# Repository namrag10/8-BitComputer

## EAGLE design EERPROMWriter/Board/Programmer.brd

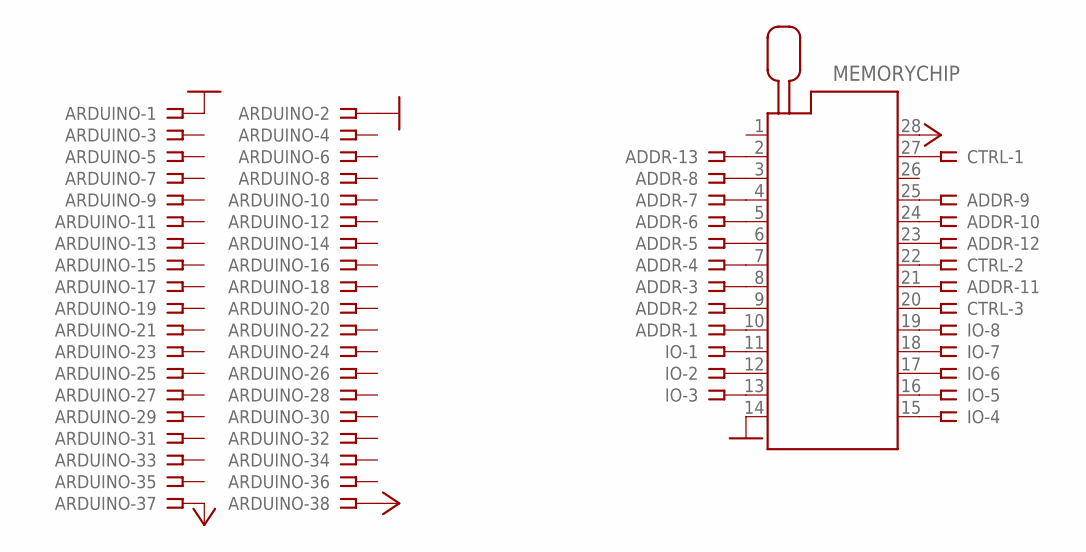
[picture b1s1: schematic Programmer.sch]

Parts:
ADDR: SSW-113-02-G-S-RA
ARDUINO: SSW-119-02-G-D
CTRL: SSW-103-02-G-S-RA
IO: SSW-108-02-G-S-RA
MEMORYCHIP: 228-1277-00-0602J

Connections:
GND: ARDUINO.1, ARDUINO.2, MEMORYCHIP.14
unnamed: IO.1, MEMORYCHIP.11
unnamed: IO.2, MEMORYCHIP.12
unnamed: IO.3, MEMORYCHIP.13
unnamed: IO.4, MEMORYCHIP.15
unnamed: IO.5, MEMORYCHIP.16
unnamed: IO.6, MEMORYCHIP.17
unnamed: IO.7, MEMORYCHIP.18
unnamed: IO.8, MEMORYCHIP.19
unnamed: ADDR.1, MEMORYCHIP.10
unnamed: ADDR.2, MEMORYCHIP.9
unnamed: ADDR.3, MEMORYCHIP.8
unnamed: ADDR.4, MEMORYCHIP.7
unnamed: ADDR.5, MEMORYCHIP.6
unnamed: ADDR.6, MEMORYCHIP.5
unnamed: ADDR.7, MEMORYCHIP.4
unnamed: ADDR.8, MEMORYCHIP.3
unnamed: ADDR.9, MEMORYCHIP.25
unnamed: ADDR.10, MEMORYCHIP.24
unnamed: ADDR.11, MEMORYCHIP.21
unnamed: ADDR.12, MEMORYCHIP.23
unnamed: ADDR.13, MEMORYCHIP.2
unnamed: CTRL.1, MEMORYCHIP.27
unnamed: CTRL.2, MEMORYCHIP.22
unnamed: CTRL.3, MEMORYCHIP.20
VCC: ARDUINO.37, ARDUINO.38, MEMORYCHIP.28

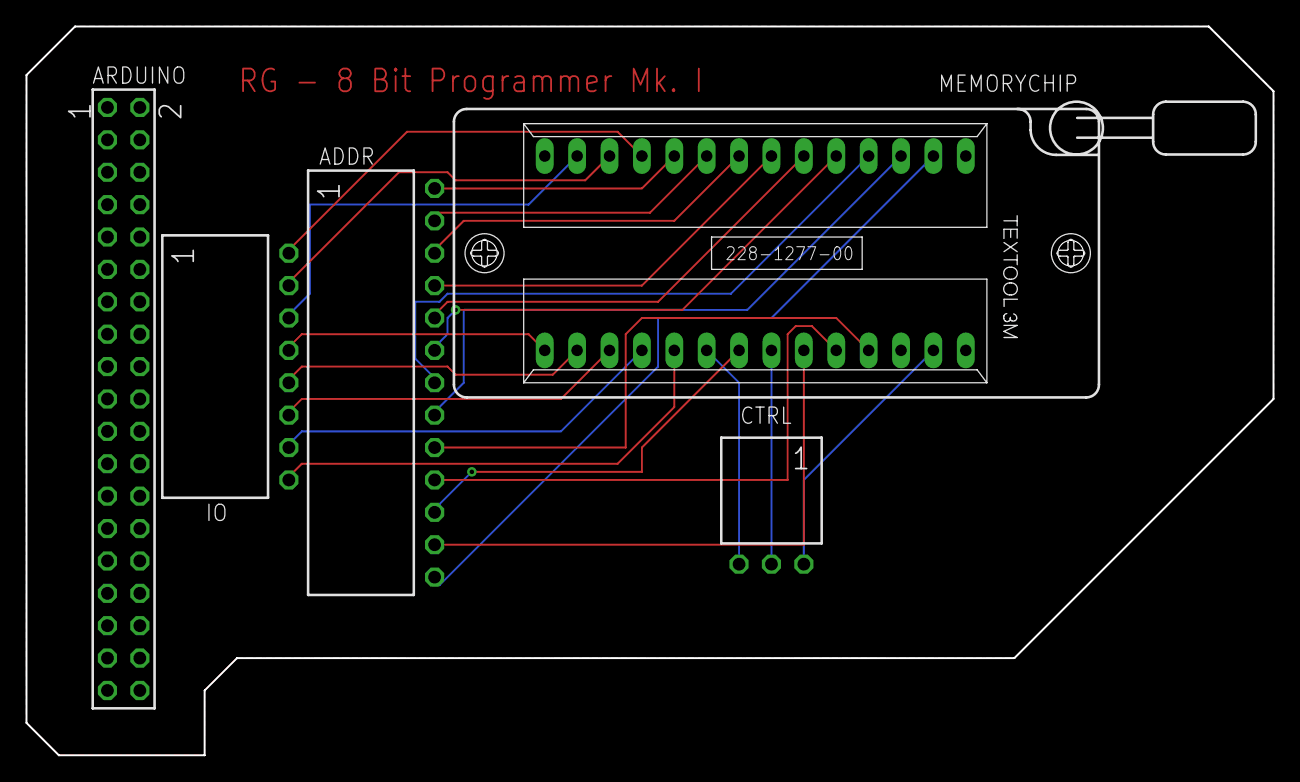
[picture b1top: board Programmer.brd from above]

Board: 2 copper layers, 97.8 x 57.1 mm, 5 parts (0 on the bottom side), 26 nets.

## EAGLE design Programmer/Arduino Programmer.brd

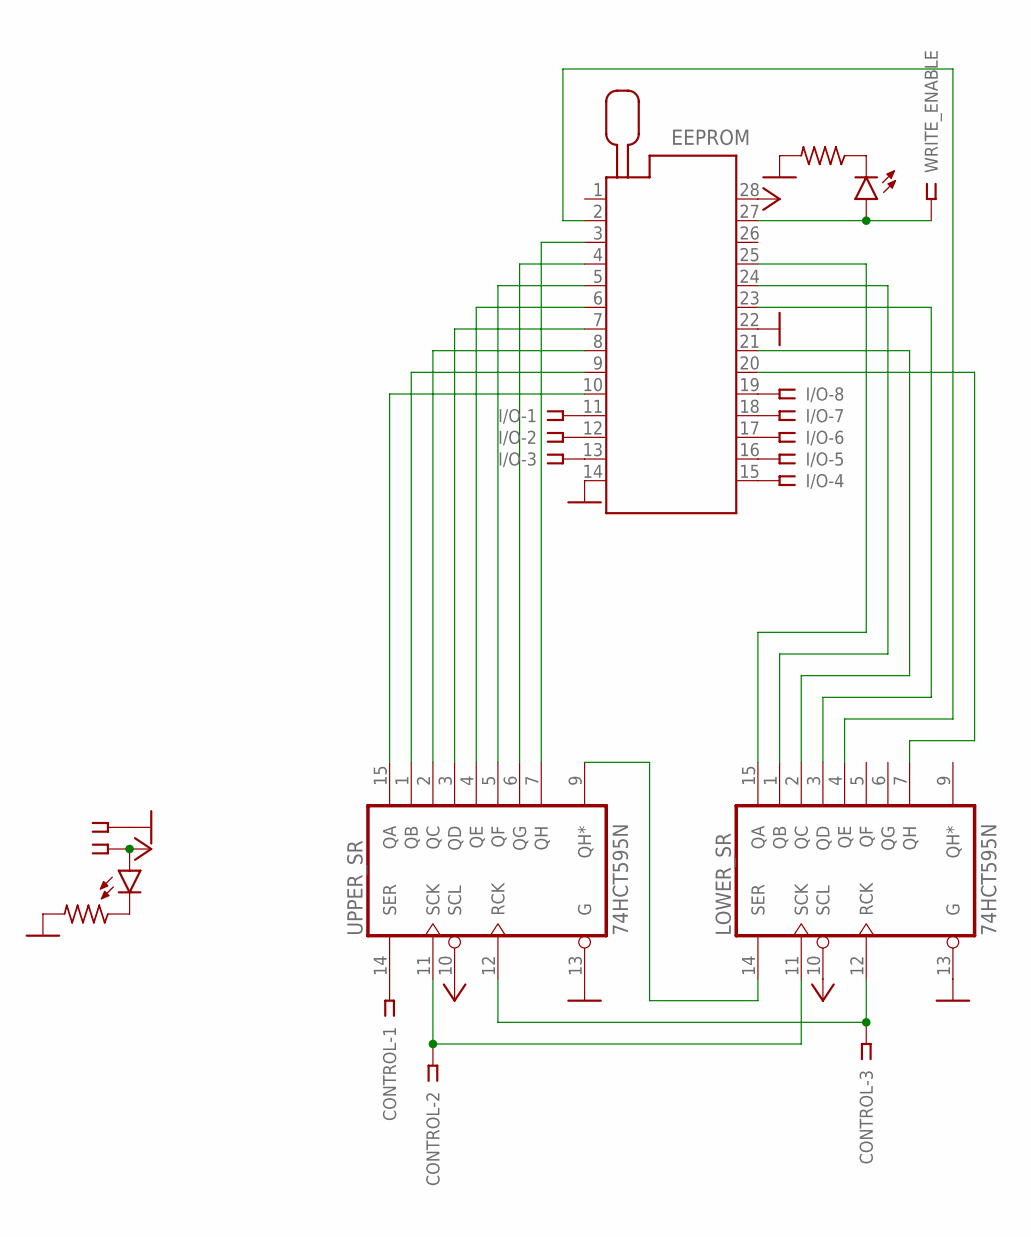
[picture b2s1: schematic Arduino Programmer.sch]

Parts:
CLK: LED5MM
CONTROL: SSW-101-02-G-T
EEPROM: 228-1277-00-0602J
I/O: SSW-108-02-G-S
LOWER_SR: 74HCT595N; DIL16
POWER: LED5MM
R1, R2: R-US_0204/7; 0204/7
UPPER_SR: 74HCT595N; DIL16
WRITE_ENABLE: SSW-101-02-G-S
X2: SSW-102-02-G-S

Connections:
GND: EEPROM.14, EEPROM.22, LOWER_SR.8 (GND), LOWER_SR.13 (G), R1.2, R2.2, UPPER_SR.8 (GND), UPPER_SR.13 (G), X2.1
unnamed: CONTROL.3, LOWER_SR.12 (RCK), UPPER_SR.12 (RCK)
unnamed: CONTROL.2, LOWER_SR.11 (SCK), UPPER_SR.11 (SCK)
unnamed: LOWER_SR.14 (SER), UPPER_SR.9 (QH*)
unnamed: CONTROL.1, UPPER_SR.14 (SER)
unnamed: EEPROM.10, UPPER_SR.15 (QA)
unnamed: EEPROM.9, UPPER_SR.1 (QB)
unnamed: EEPROM.8, UPPER_SR.2 (QC)
unnamed: EEPROM.7, UPPER_SR.3 (QD)
unnamed: EEPROM.6, UPPER_SR.4 (QE)
unnamed: EEPROM.5, UPPER_SR.5 (QF)
unnamed: EEPROM.4, UPPER_SR.6 (QG)
unnamed: EEPROM.3, UPPER_SR.7 (QH)
unnamed: EEPROM.25, LOWER_SR.15 (QA)
unnamed: EEPROM.24, LOWER_SR.1 (QB)
unnamed: EEPROM.21, LOWER_SR.2 (QC)
unnamed: EEPROM.23, LOWER_SR.3 (QD)
unnamed: EEPROM.2, LOWER_SR.4 (QE)
unnamed: EEPROM.20, LOWER_SR.7 (QH)
unnamed: EEPROM.16, I/O.5
unnamed: EEPROM.17, I/O.6
unnamed: EEPROM.18, I/O.7
unnamed: EEPROM.19, I/O.8
unnamed: EEPROM.11, I/O.1
unnamed: EEPROM.12, I/O.2
unnamed: EEPROM.13, I/O.3
unnamed: EEPROM.15, I/O.4
unnamed: CLK.A, EEPROM.27, WRITE_ENABLE.1
unnamed: CLK.K (C), R1.1
unnamed: POWER.K (C), R2.1
VCC: EEPROM.28, LOWER_SR.10 (SCL), LOWER_SR.16 (VCC), POWER.A, UPPER_SR.10 (SCL), UPPER_SR.16 (VCC), X2.2

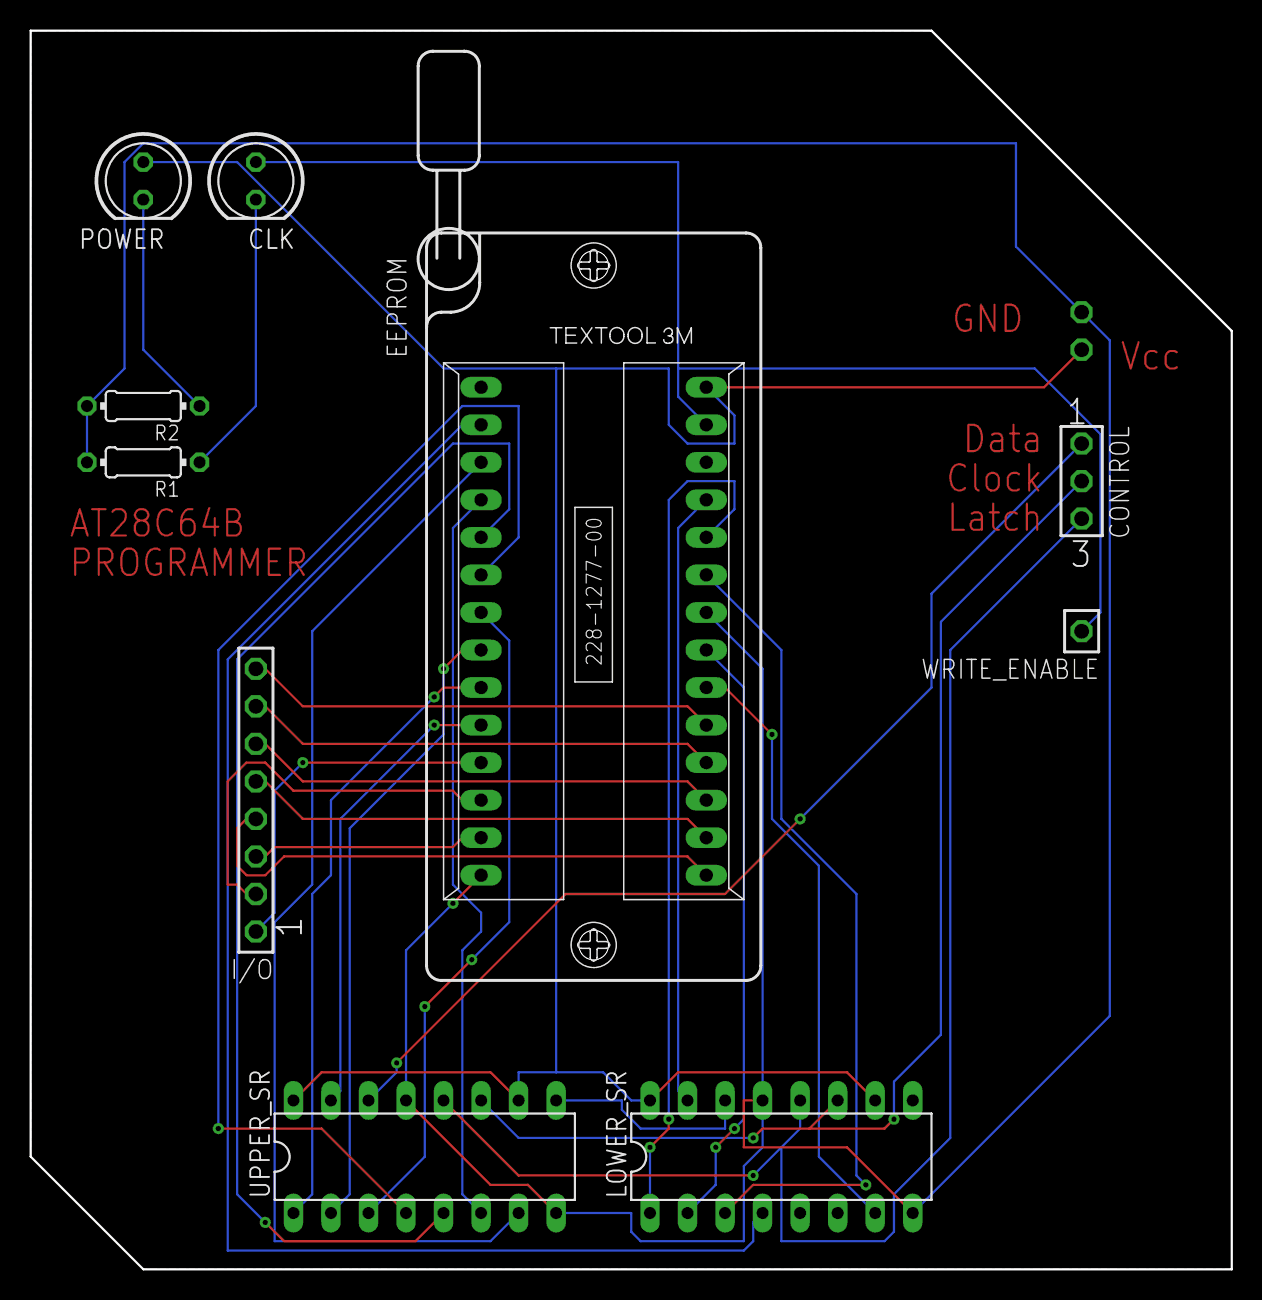
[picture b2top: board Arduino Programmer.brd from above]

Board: 2 copper layers, 81.3 x 83.8 mm, 11 parts (1 on the bottom side), 31 nets.

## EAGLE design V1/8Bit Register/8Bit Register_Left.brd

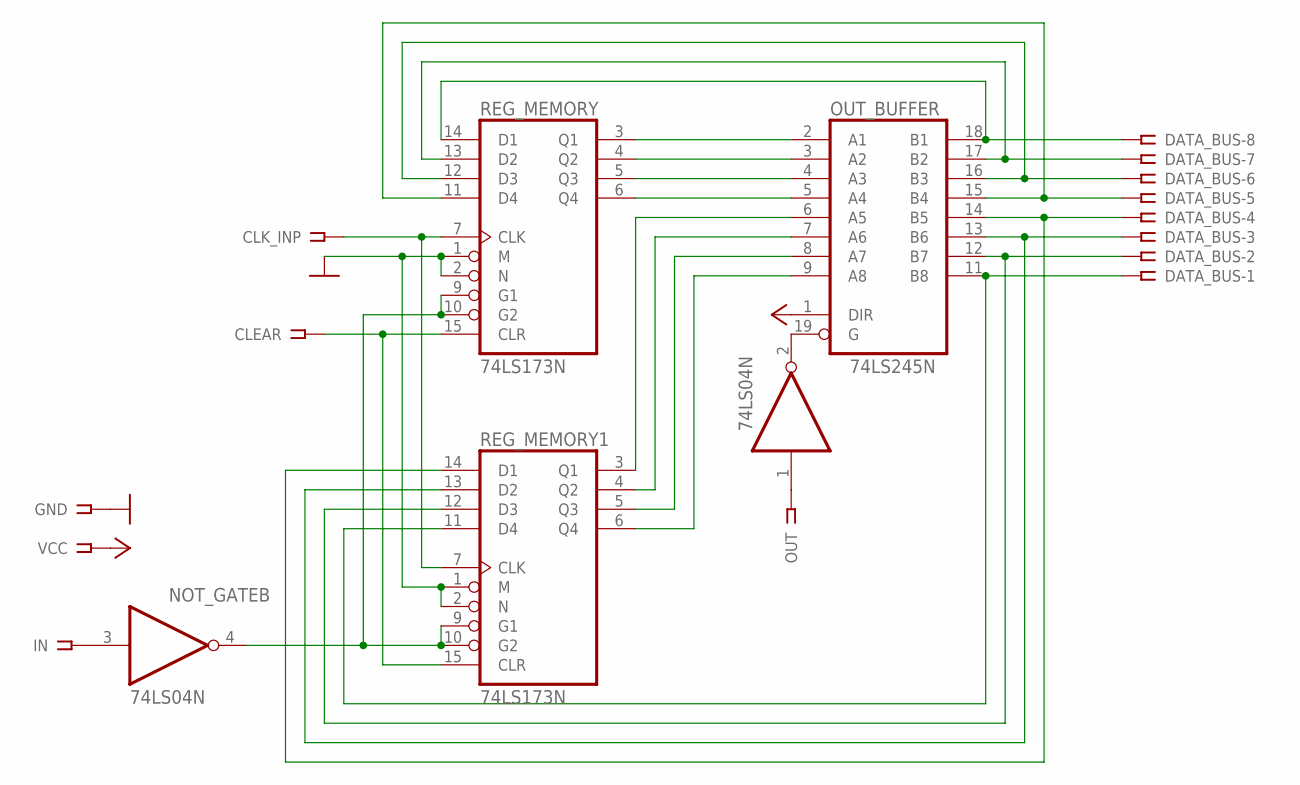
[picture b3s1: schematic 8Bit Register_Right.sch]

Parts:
CLEAR: SSW-101-02-G-S-RA
CLK_INP: SSW-101-02-G-S-RA
DATA_BUS: SSW-108-02-G-S
GND: SSW-101-02-G-S-RA
IN: SSW-101-02-G-S-RA
NOT_GATE: 74LS04N; DIL14
OUT: SSW-101-02-G-S-RA
OUT_BUFFER: 74LS245N; DIL20
REG_MEMORY, REG_MEMORY1: 74LS173N; DIL16
VCC: SSW-101-02-G-S-RA

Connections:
GND: GND.1, NOT_GATE.7 (GND), OUT_BUFFER.10 (GND), REG_MEMORY.1 (M), REG_MEMORY.2 (N), REG_MEMORY.8 (GND), REG_MEMORY1.1 (M), REG_MEMORY1.2 (N), REG_MEMORY1.8 (GND)
unnamed: CLK_INP.1, REG_MEMORY.7 (CLK), REG_MEMORY1.7 (CLK)
unnamed: NOT_GATE.1 (I), OUT.1
unnamed: CLEAR.1, REG_MEMORY.15 (CLR), REG_MEMORY1.15 (CLR)
unnamed: OUT_BUFFER.2 (A1), REG_MEMORY.3 (Q1)
unnamed: OUT_BUFFER.3 (A2), REG_MEMORY.4 (Q2)
unnamed: OUT_BUFFER.4 (A3), REG_MEMORY.5 (Q3)
unnamed: OUT_BUFFER.5 (A4), REG_MEMORY.6 (Q4)
unnamed: OUT_BUFFER.6 (A5), REG_MEMORY1.3 (Q1)
unnamed: OUT_BUFFER.7 (A6), REG_MEMORY1.4 (Q2)
unnamed: OUT_BUFFER.8 (A7), REG_MEMORY1.5 (Q3)
unnamed: OUT_BUFFER.9 (A8), REG_MEMORY1.6 (Q4)
unnamed: NOT_GATE.2 (O), OUT_BUFFER.19 (G)
unnamed: DATA_BUS.8, OUT_BUFFER.18 (B1), REG_MEMORY.14 (D1)
unnamed: DATA_BUS.7, OUT_BUFFER.17 (B2), REG_MEMORY.13 (D2)
unnamed: NOT_GATE.4 (O), REG_MEMORY.9 (G1), REG_MEMORY.10 (G2), REG_MEMORY1.9 (G1), REG_MEMORY1.10 (G2)
unnamed: DATA_BUS.6, OUT_BUFFER.16 (B3), REG_MEMORY.12 (D3)
unnamed: DATA_BUS.5, OUT_BUFFER.15 (B4), REG_MEMORY.11 (D4)
unnamed: DATA_BUS.1, OUT_BUFFER.11 (B8), REG_MEMORY1.11 (D4)
unnamed: DATA_BUS.2, OUT_BUFFER.12 (B7), REG_MEMORY1.12 (D3)
unnamed: DATA_BUS.3, OUT_BUFFER.13 (B6), REG_MEMORY1.13 (D2)
unnamed: DATA_BUS.4, OUT_BUFFER.14 (B5), REG_MEMORY1.14 (D1)
unnamed: IN.1, NOT_GATE.3 (I)
VCC: NOT_GATE.14 (VCC), OUT_BUFFER.1 (DIR), OUT_BUFFER.20 (VCC), REG_MEMORY.16 (VCC), REG_MEMORY1.16 (VCC), VCC.1

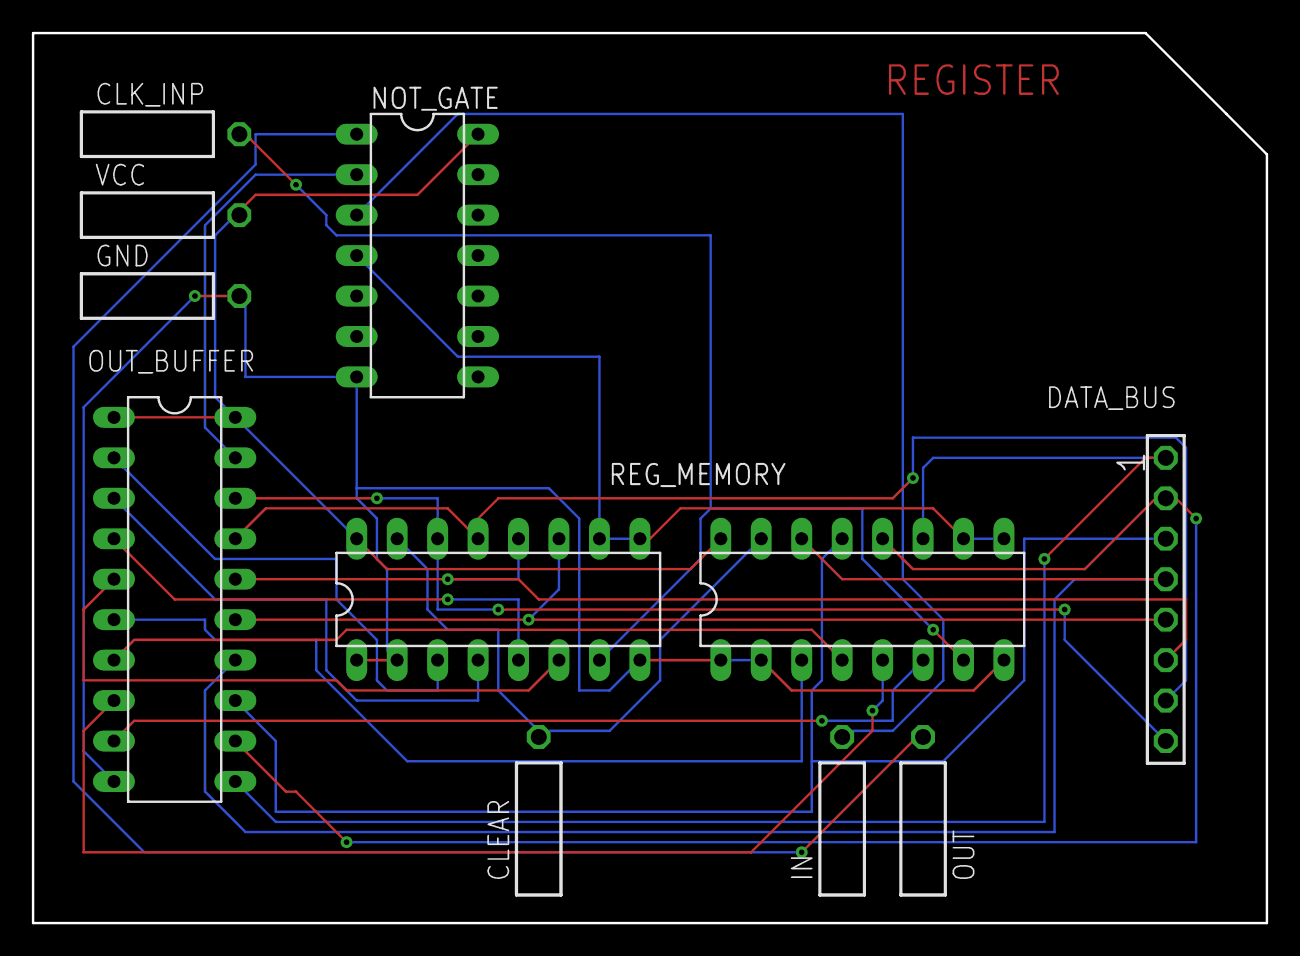
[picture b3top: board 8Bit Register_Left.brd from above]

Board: 2 copper layers, 77.5 x 55.9 mm, 11 parts (0 on the bottom side), 24 nets.

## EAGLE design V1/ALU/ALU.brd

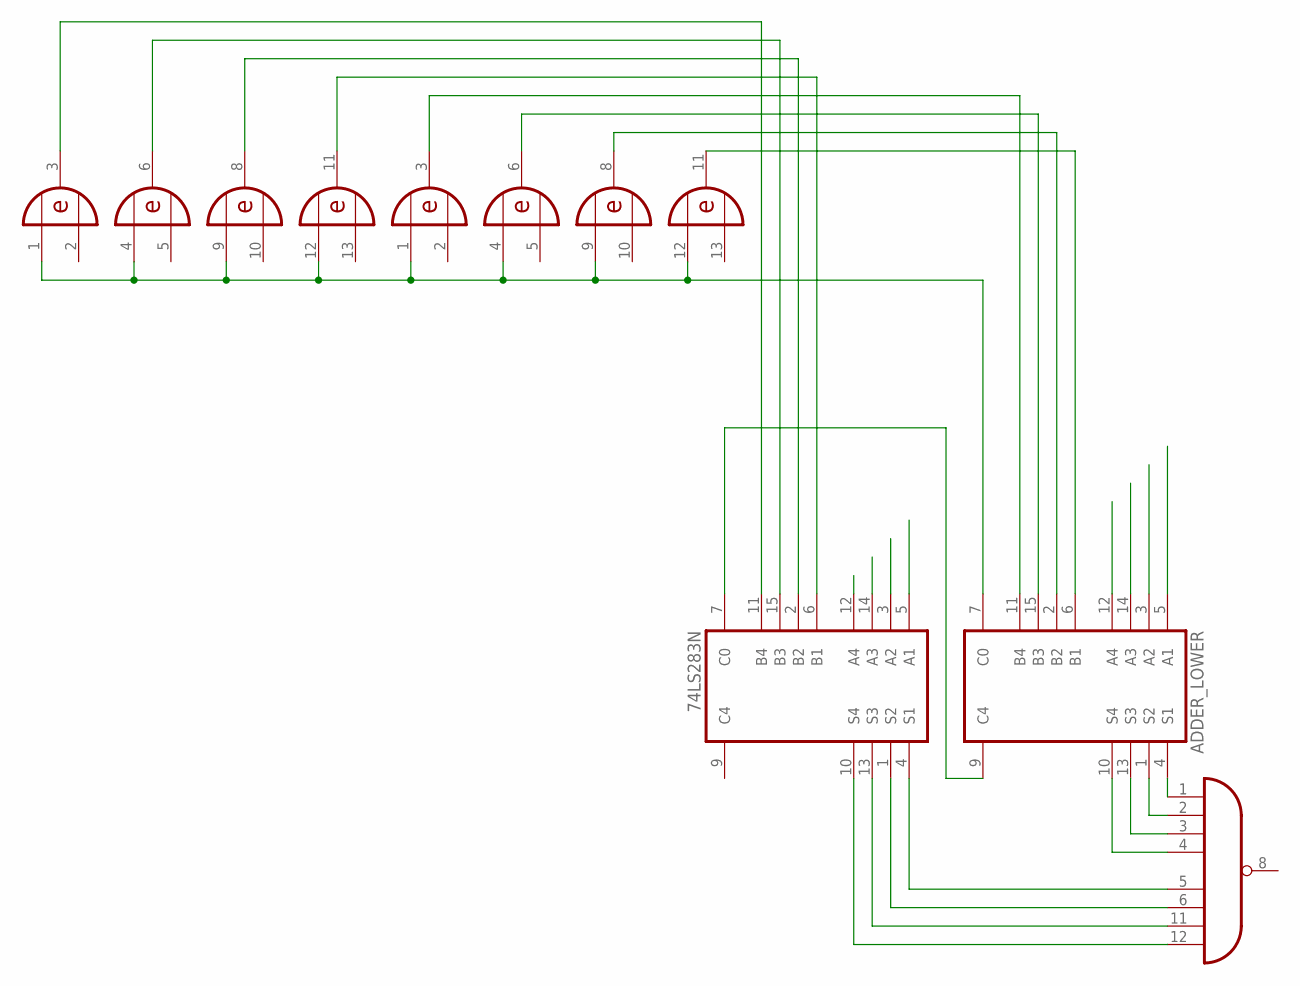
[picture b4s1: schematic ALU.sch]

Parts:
ADDER_LOWER: 74LS283N; DIL16
ADDER_UPPER: 74LS283N; DIL16
AND_GATE1: 74LS30N; DIL14
SUBTRACT_INVERTER_LOWER: 74LS86N; DIL14
SUBTRACT_INVERTER_UPPER: 74LS86N; DIL14

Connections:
GND: ADDER_LOWER.8 (GND), ADDER_UPPER.8 (GND), AND_GATE1.7 (GND), SUBTRACT_INVERTER_LOWER.7 (GND), SUBTRACT_INVERTER_UPPER.7 (GND)
unnamed: ADDER_LOWER.10 (S4), AND_GATE1.4 (I3)
unnamed: ADDER_LOWER.13 (S3), AND_GATE1.3 (I2)
unnamed: ADDER_LOWER.1 (S2), AND_GATE1.2 (I1)
unnamed: ADDER_LOWER.4 (S1), AND_GATE1.1 (I0)
unnamed: ADDER_LOWER.6 (B1), SUBTRACT_INVERTER_LOWER.11 (O)
unnamed: ADDER_LOWER.2 (B2), SUBTRACT_INVERTER_LOWER.8 (O)
unnamed: ADDER_LOWER.15 (B3), SUBTRACT_INVERTER_LOWER.6 (O)
unnamed: ADDER_LOWER.11 (B4), SUBTRACT_INVERTER_LOWER.3 (O)
unnamed: ADDER_UPPER.6 (B1), SUBTRACT_INVERTER_UPPER.11 (O)
unnamed: ADDER_UPPER.2 (B2), SUBTRACT_INVERTER_UPPER.8 (O)
unnamed: ADDER_UPPER.15 (B3), SUBTRACT_INVERTER_UPPER.6 (O)
unnamed: ADDER_UPPER.11 (B4), SUBTRACT_INVERTER_UPPER.3 (O)
REG_A_1PLACE: ADDER_LOWER.5 (A1)
REG_A_2PLACE: ADDER_LOWER.3 (A2)
REG_A_4PLACE: ADDER_LOWER.14 (A3)
REG_A_8PLACE: ADDER_LOWER.12 (A4)
REG_A_16PLACE: ADDER_UPPER.5 (A1)
REG_A_32PLACE: ADDER_UPPER.3 (A2)
REG_A_64PLACE: ADDER_UPPER.14 (A3)
REG_A_128PLACE: ADDER_UPPER.12 (A4)
SUBTRACT: ADDER_LOWER.7 (C0), SUBTRACT_INVERTER_LOWER.1 (I0), SUBTRACT_INVERTER_LOWER.4 (I0), SUBTRACT_INVERTER_LOWER.9 (I0), SUBTRACT_INVERTER_LOWER.12 (I0), SUBTRACT_INVERTER_UPPER.1 (I0), SUBTRACT_INVERTER_UPPER.4 (I0), SUBTRACT_INVERTER_UPPER.9 (I0), SUBTRACT_INVERTER_UPPER.12 (I0)
SUM_16: ADDER_UPPER.4 (S1), AND_GATE1.5 (I4)
SUM_32: ADDER_UPPER.1 (S2), AND_GATE1.6 (I5)
SUM_64: ADDER_UPPER.13 (S3), AND_GATE1.11 (I6)
SUM_128: ADDER_UPPER.10 (S4), AND_GATE1.12 (I7)
SUM_CARRY: ADDER_LOWER.9 (C4), ADDER_UPPER.7 (C0)
VCC: ADDER_LOWER.16 (VCC), ADDER_UPPER.16 (VCC), AND_GATE1.14 (VCC), SUBTRACT_INVERTER_LOWER.14 (VCC), SUBTRACT_INVERTER_UPPER.14 (VCC)

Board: 2 copper layers, 5 parts (0 on the bottom side), 20 nets, no tracks yet.

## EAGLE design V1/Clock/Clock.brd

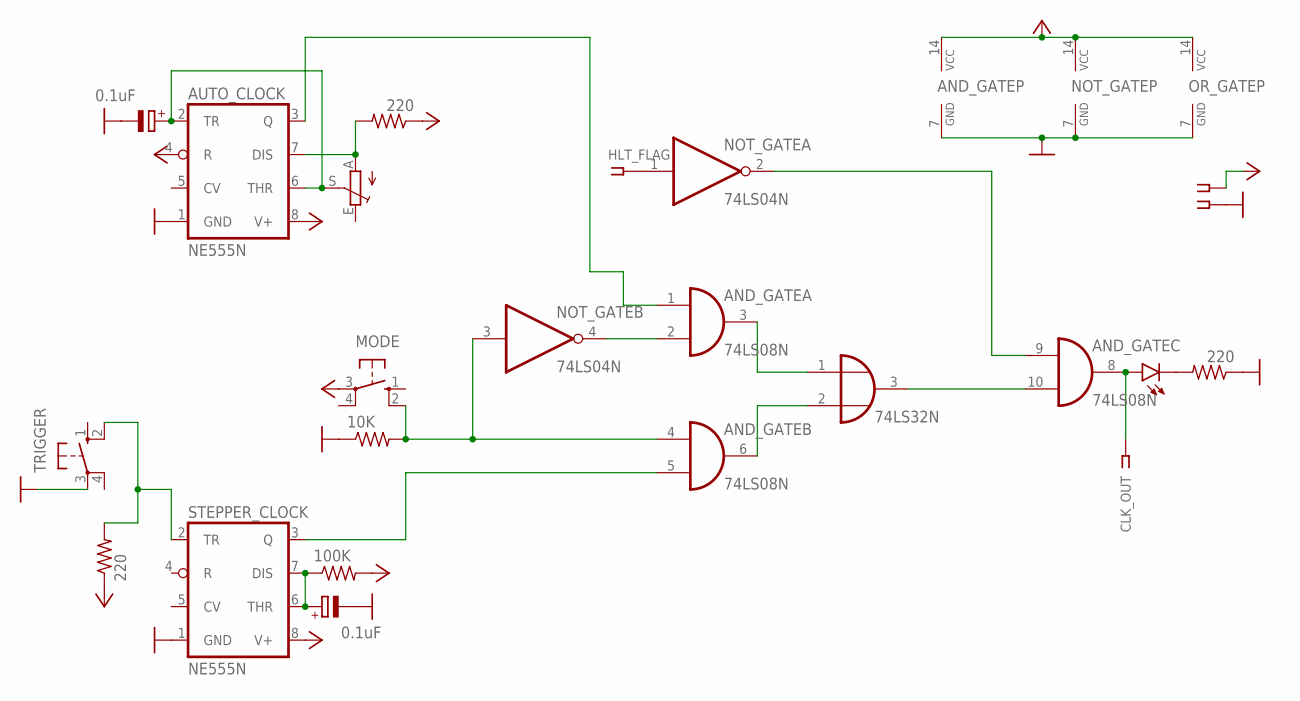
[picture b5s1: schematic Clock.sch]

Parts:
AND_GATE: 74LS08N; DIL14
AUTO_CLOCK: NE555N; DIL08
C1, C2: 0.1uF; E2-5
CLK_OUT: SSW-101-02-G-S-RA
CLOCK: LED5MM
FREQUENCY: TRIM_EU-RJ9W; RJ9W
GND: SSW-101-02-G-S-RA
HLT_FLAG: SSW-101-02-G-S-RA
MODE: 10-XX; B3F-10XX
NOT_GATE: 74LS04N; DIL14
OR_GATE: 74LS32N; DIL14
R2, R5, R6: 220; 0204/7
R3: 100K; 0204/7
R4: 10K; 0204/7
STEPPER_CLOCK: NE555N; DIL08
TRIGGER: 10-XX; B3F-10XX
VCC: SSW-101-02-G-S-RA

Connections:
+5V: AND_GATE.14 (VCC), AUTO_CLOCK.4 (R), AUTO_CLOCK.8 (V+), MODE.3, NOT_GATE.14 (VCC), OR_GATE.14 (VCC), R2.1, R3.2, R6.1, STEPPER_CLOCK.8 (V+), VCC.1
GND: AND_GATE.7 (GND), AUTO_CLOCK.1 (GND), C1.-, C2.-, GND.1, NOT_GATE.7 (GND), OR_GATE.7 (GND), R4.1, R5.1, STEPPER_CLOCK.1 (GND), TRIGGER.3
unnamed: C2.+, R3.1, STEPPER_CLOCK.6 (THR), STEPPER_CLOCK.7 (DIS)
unnamed: R2.2, STEPPER_CLOCK.2 (TR), TRIGGER.2 (S1)
unnamed: CLOCK.K (C), R5.2
unnamed: AND_GATE.5 (I1), STEPPER_CLOCK.3 (Q)
unnamed: AUTO_CLOCK.2 (TR), AUTO_CLOCK.6 (THR), C1.+, FREQUENCY.S
unnamed: AND_GATE.1 (I0), AUTO_CLOCK.3 (Q)
unnamed: AND_GATE.8 (O), CLK_OUT.1, CLOCK.A
unnamed: AND_GATE.2 (I1), NOT_GATE.4 (O)
unnamed: AND_GATE.4 (I0), MODE.2 (S1), NOT_GATE.3 (I), R4.2
unnamed: AND_GATE.10 (I1), OR_GATE.3 (O)
unnamed: AND_GATE.9 (I0), NOT_GATE.2 (O)
unnamed: AND_GATE.3 (O), OR_GATE.1 (I0)
unnamed: AND_GATE.6 (O), OR_GATE.2 (I1)
unnamed: HLT_FLAG.1, NOT_GATE.1 (I)
unnamed: AUTO_CLOCK.7 (DIS), FREQUENCY.A, R6.2

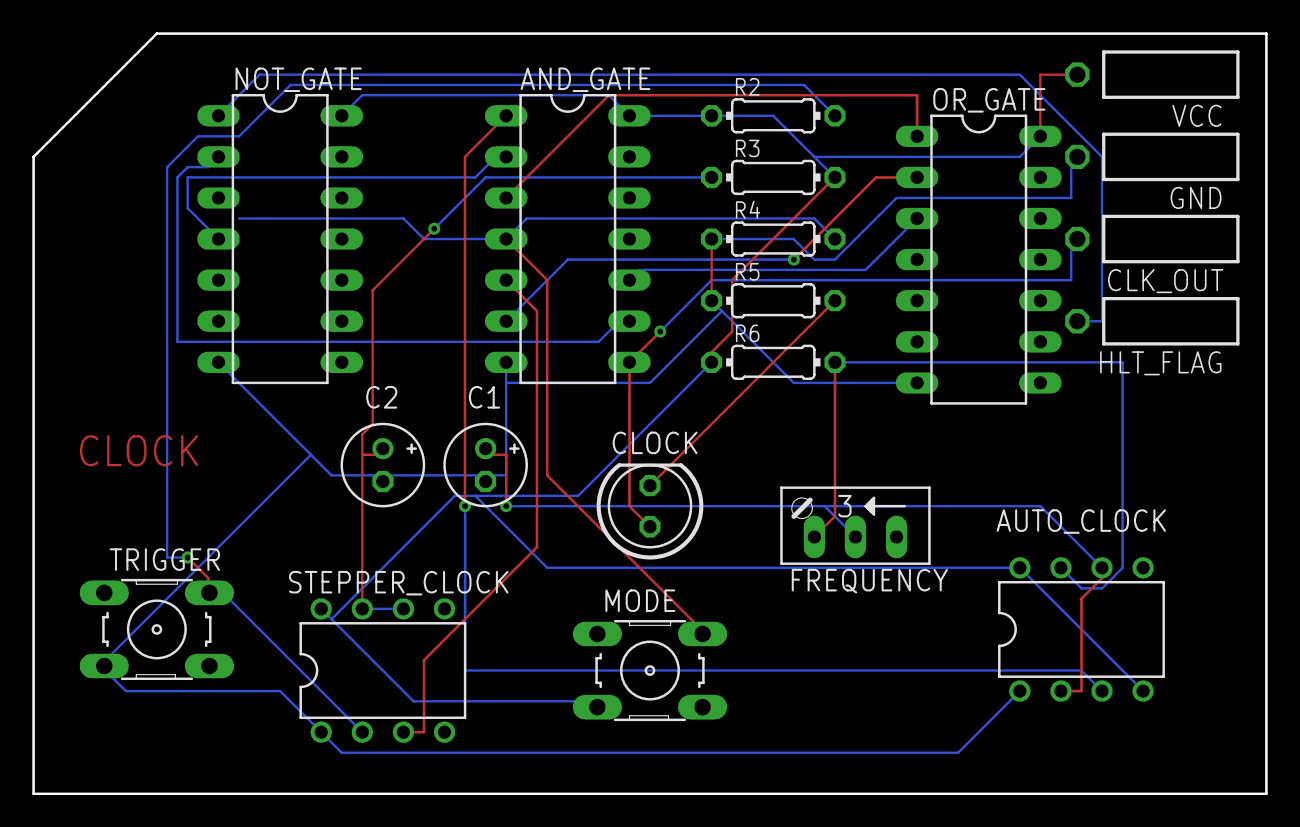
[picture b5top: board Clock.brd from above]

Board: 2 copper layers, 76.2 x 47.0 mm, 20 parts (0 on the bottom side), 17 nets.

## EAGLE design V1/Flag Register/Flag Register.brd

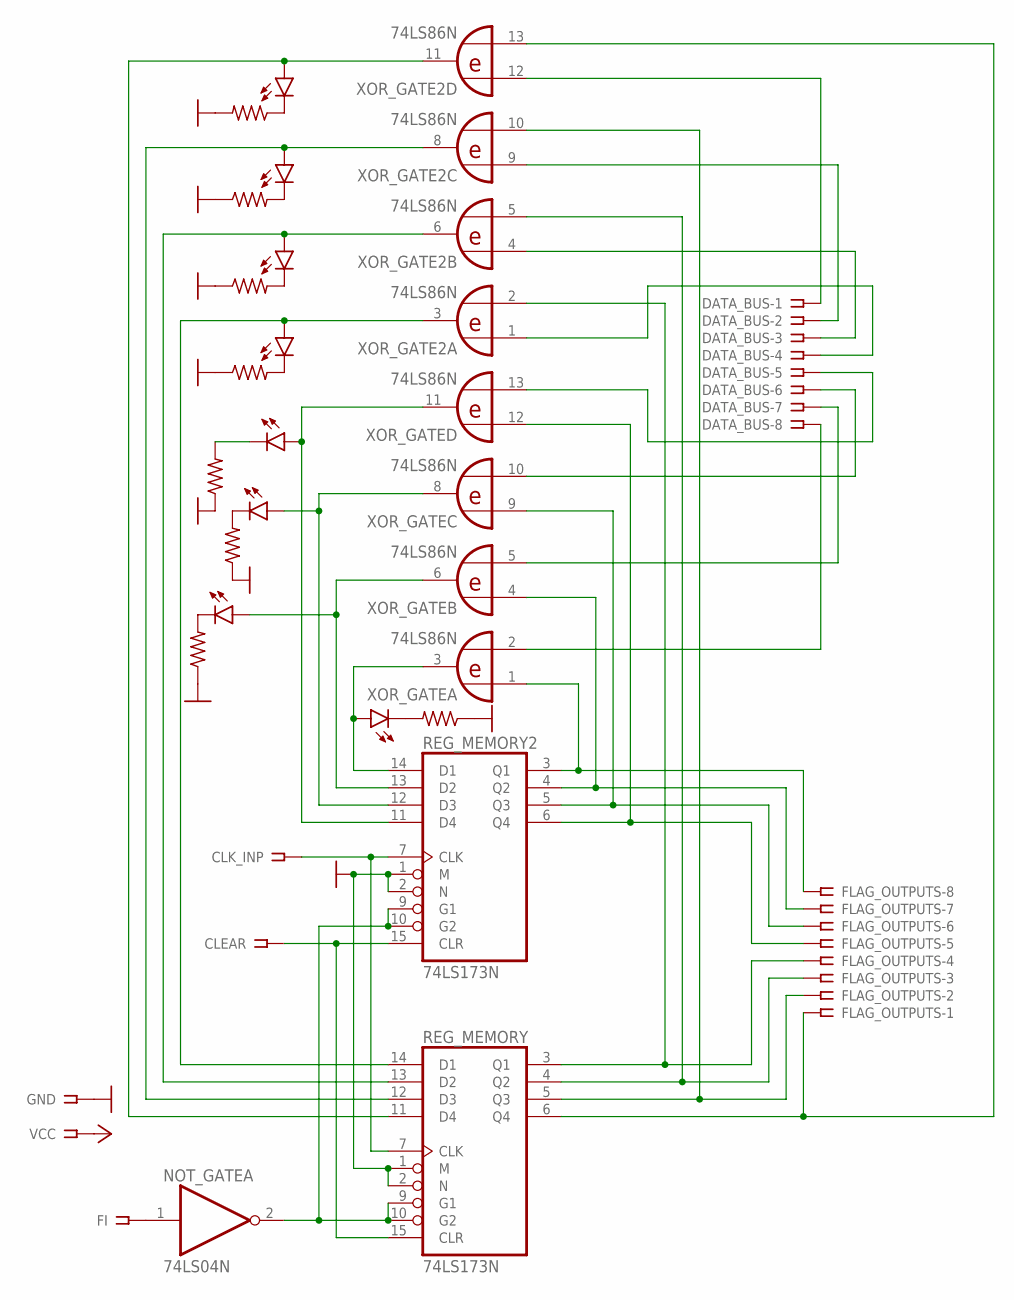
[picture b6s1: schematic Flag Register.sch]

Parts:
CLEAR: SSW-101-02-G-S-RA
CLK_INP: SSW-101-02-G-S-RA
DATA_BUS: SSW-108-02-G-S
FI: SSW-101-02-G-S-RA
FLAG_OUTPUTS: SSW-108-02-G-S
GND: SSW-101-02-G-S-RA
LED1, LED2, LED3, LED4, LED5, LED6, LED7, LED8: LED5MM
NOT_GATE: 74LS04N; DIL14
R2, R3, R4, R5, R6, R7, R8, R9: 220; 0204/7
REG_MEMORY, REG_MEMORY2: 74LS173N; DIL16
VCC: SSW-101-02-G-S-RA
XOR_GATE, XOR_GATE2: 74LS86N; DIL14

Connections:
GND: GND.1, NOT_GATE.7 (GND), R2.2, R3.1, R4.1, R5.1, R6.1, R7.1, R8.1, R9.1, REG_MEMORY.1 (M), REG_MEMORY.2 (N), REG_MEMORY.8 (GND), REG_MEMORY2.1 (M), REG_MEMORY2.2 (N), REG_MEMORY2.8 (GND), XOR_GATE.7 (GND), XOR_GATE2.7 (GND)
unnamed: CLK_INP.1, REG_MEMORY.7 (CLK), REG_MEMORY2.7 (CLK)
unnamed: FLAG_OUTPUTS.8, REG_MEMORY2.3 (Q1), XOR_GATE.1 (I0)
unnamed: CLEAR.1, REG_MEMORY.15 (CLR), REG_MEMORY2.15 (CLR)
unnamed: FLAG_OUTPUTS.7, REG_MEMORY2.4 (Q2), XOR_GATE.4 (I0)
unnamed: FLAG_OUTPUTS.6, REG_MEMORY2.5 (Q3), XOR_GATE.9 (I0)
unnamed: FLAG_OUTPUTS.5, REG_MEMORY2.6 (Q4), XOR_GATE.12 (I0)
unnamed: FLAG_OUTPUTS.1, REG_MEMORY.6 (Q4), XOR_GATE2.13 (I1)
unnamed: FLAG_OUTPUTS.2, REG_MEMORY.5 (Q3), XOR_GATE2.10 (I1)
unnamed: FLAG_OUTPUTS.3, REG_MEMORY.4 (Q2), XOR_GATE2.5 (I1)
unnamed: FLAG_OUTPUTS.4, REG_MEMORY.3 (Q1), XOR_GATE2.2 (I1)
unnamed: DATA_BUS.8, XOR_GATE.2 (I1)
unnamed: DATA_BUS.7, XOR_GATE.5 (I1)
unnamed: DATA_BUS.6, XOR_GATE.10 (I1)
unnamed: DATA_BUS.5, XOR_GATE.13 (I1)
unnamed: NOT_GATE.2 (O), REG_MEMORY.9 (G1), REG_MEMORY.10 (G2), REG_MEMORY2.9 (G1), REG_MEMORY2.10 (G2)
unnamed: DATA_BUS.4, XOR_GATE2.1 (I0)
unnamed: DATA_BUS.3, XOR_GATE2.4 (I0)
unnamed: DATA_BUS.2, XOR_GATE2.9 (I0)
unnamed: DATA_BUS.1, XOR_GATE2.12 (I0)
unnamed: LED2.K (C), R3.2
unnamed: LED8.A, REG_MEMORY2.14 (D1), XOR_GATE.3 (O)
unnamed: LED7.A, REG_MEMORY2.13 (D2), XOR_GATE.6 (O)
unnamed: LED6.A, REG_MEMORY2.12 (D3), XOR_GATE.8 (O)
unnamed: LED5.A, REG_MEMORY2.11 (D4), XOR_GATE.11 (O)
unnamed: LED4.A, REG_MEMORY.14 (D1), XOR_GATE2.3 (O)
unnamed: LED3.A, REG_MEMORY.13 (D2), XOR_GATE2.6 (O)
unnamed: LED2.A, REG_MEMORY.12 (D3), XOR_GATE2.8 (O)
unnamed: LED1.A, REG_MEMORY.11 (D4), XOR_GATE2.11 (O)
unnamed: LED3.K (C), R4.2
unnamed: LED4.K (C), R5.2
unnamed: LED5.K (C), R6.2
unnamed: LED6.K (C), R7.2
unnamed: LED7.K (C), R8.2
unnamed: LED8.K (C), R9.2
unnamed: LED1.K (C), R2.1
unnamed: FI.1, NOT_GATE.1 (I)
VCC: NOT_GATE.14 (VCC), REG_MEMORY.16 (VCC), REG_MEMORY2.16 (VCC), VCC.1, XOR_GATE.14 (VCC), XOR_GATE2.14 (VCC)

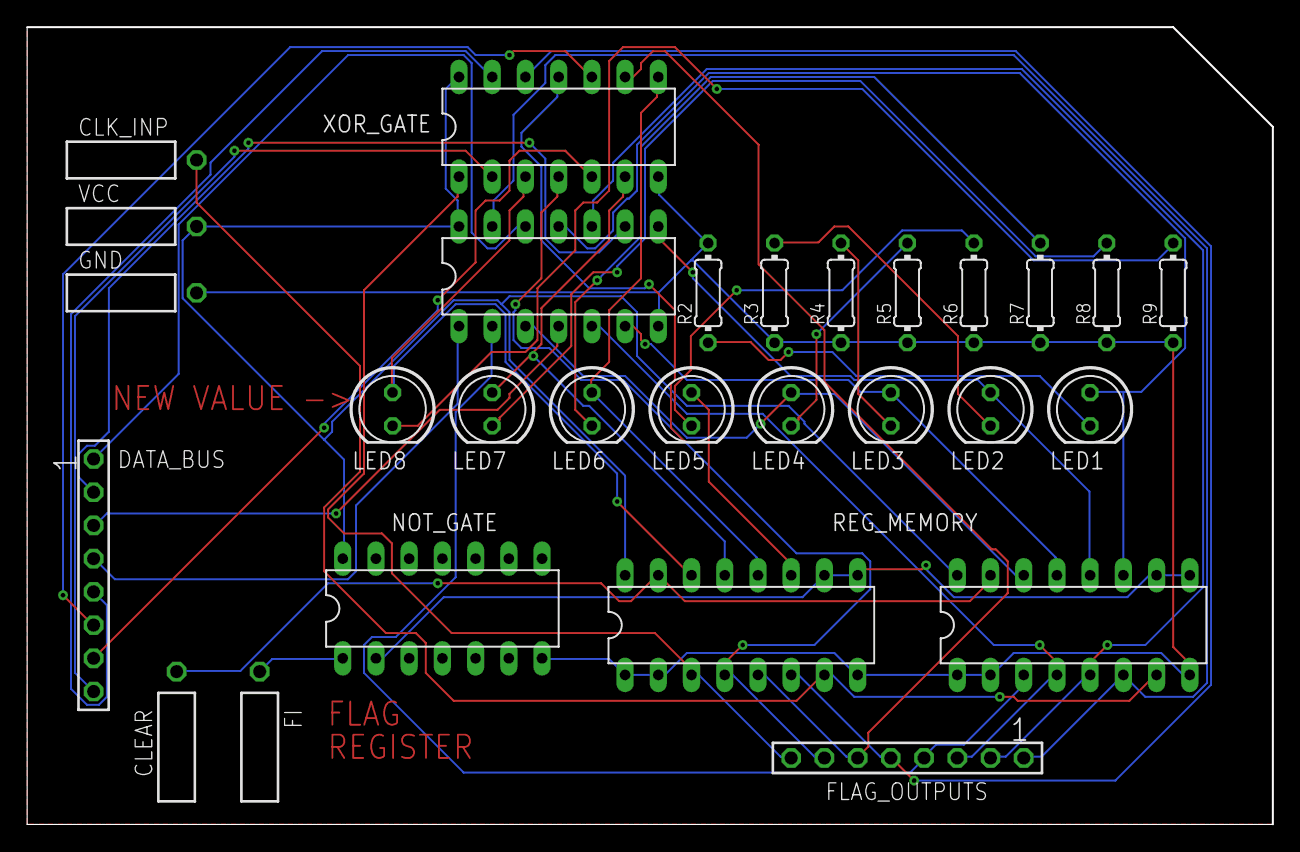
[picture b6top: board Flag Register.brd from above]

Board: 2 copper layers, 95.2 x 61.0 mm, 28 parts (0 on the bottom side), 38 nets.
